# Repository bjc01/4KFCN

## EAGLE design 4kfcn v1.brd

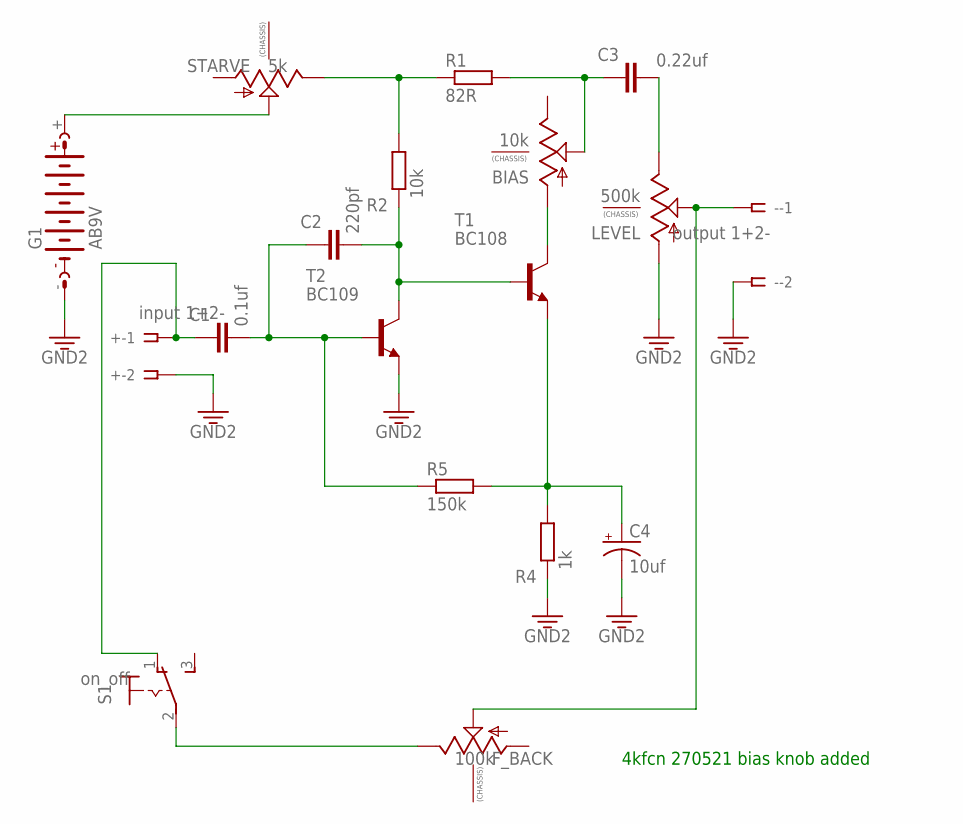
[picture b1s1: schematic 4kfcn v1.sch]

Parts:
+: input 1+2-; SSW-101-02-G-Q
-: output 1+2-; SSW-101-02-G-Q
BIAS: 10k; 9MM_SNAP-IN_POT
C1: 0.1uf; C5B3.5
C2: 220pf; C5B3.5
C3: 0.22uf; C5B3.5
C4: 10uf; CPOL-RADIAL-5MM-10MM
F_BACK: 100k; 9MM_SNAP-IN_POT
G1: AB9V
LEVEL: 500k; 9MM_SNAP-IN_POT
R1: 82R; 0207/10
R2: 10k; 0207/10
R4: 1k; 0207/10
R5: 150k; 0207/10
S1: on_off; M9040P
STARVE: 5k; 9MM_SNAP-IN_POT
T1: BC108; TO18
T2: BC109; TO18

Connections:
3.3V: +.2, -.2, C4.-, G1.-, LEVEL.1 (A), R4.1, T2.1 (E)
unnamed: C2.2, R2.1, T1.2 (B), T2.3 (C)
unnamed: BIAS.1 (A), T1.3 (C)
unnamed: C4.+, R4.2, R5.2, T1.1 (E)
unnamed: C1.2, C2.1, R5.1, T2.2 (B)
unnamed: BIAS.2 (S), C3.1, R1.2
unnamed: R1.1, R2.2, STARVE.3 (E)
unnamed: +.1, C1.1, S1.1 (O)
unnamed: C3.2, LEVEL.3 (E)
unnamed: -.1, F_BACK.2 (S), LEVEL.2 (S)
unnamed: G1.+, STARVE.2 (S)
unnamed: F_BACK.3 (E), S1.2

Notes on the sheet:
4kfcn 270521 bias knob added

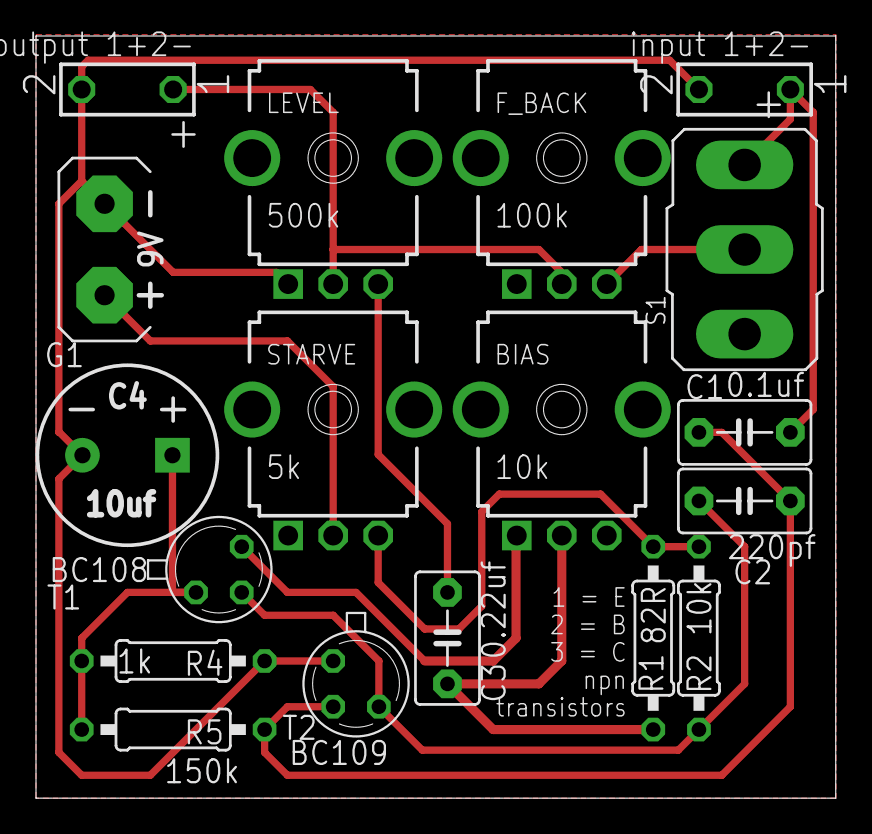
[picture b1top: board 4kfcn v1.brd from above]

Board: 2 copper layers, 44.4 x 42.3 mm, 18 parts (0 on the bottom side), 12 nets.

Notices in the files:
parts and their libraries:
SparkFun-Capacitors: Licensing: Creative Commons ShareAlike 4.0 International - https://creativecommons.org/licenses/by-sa/4.0
